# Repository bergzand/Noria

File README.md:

# Noria Split Keyboard

The Noria keyboard is a Kyria-based split keyboard. It has 6 colums and 3 rows
with a larger thumb cluster. Like the original Kyria it has support for both 2U
and dual 1U keys for the thumbs. There are three positions for a rotary encoder
of which one can be used at a time

The PCB can be flipped and used for both the left and right variant.

The PCB has space for a SPI NOR flash chip that can be used for user
configuration settings

## Design gotchas

- *When using a rotary encoder*: The pads for the chassis pins of the rotary
  encoder overlap with the pins for the push button. When using a rotary encoder
  with a push button the chassis pads must be manually detached (a simple knife
  will do) from *both* sides of the PCB.

- The microcontroller module and the SPI NOR flash must be on the same side of
  the PCB

- To use the reset pin, the User Information Configuration Register must be
  configured to pin 0.18 of the microntroller.

- The rotary encoder pins are connected to the NFC antenna pins of the
  microcontroller. As these pins are protected by default for NFC operations and
  will not function as rotary encoder pins. These protections must be disabled
  in the NFCPINS registers of the User Information Configuration Register.

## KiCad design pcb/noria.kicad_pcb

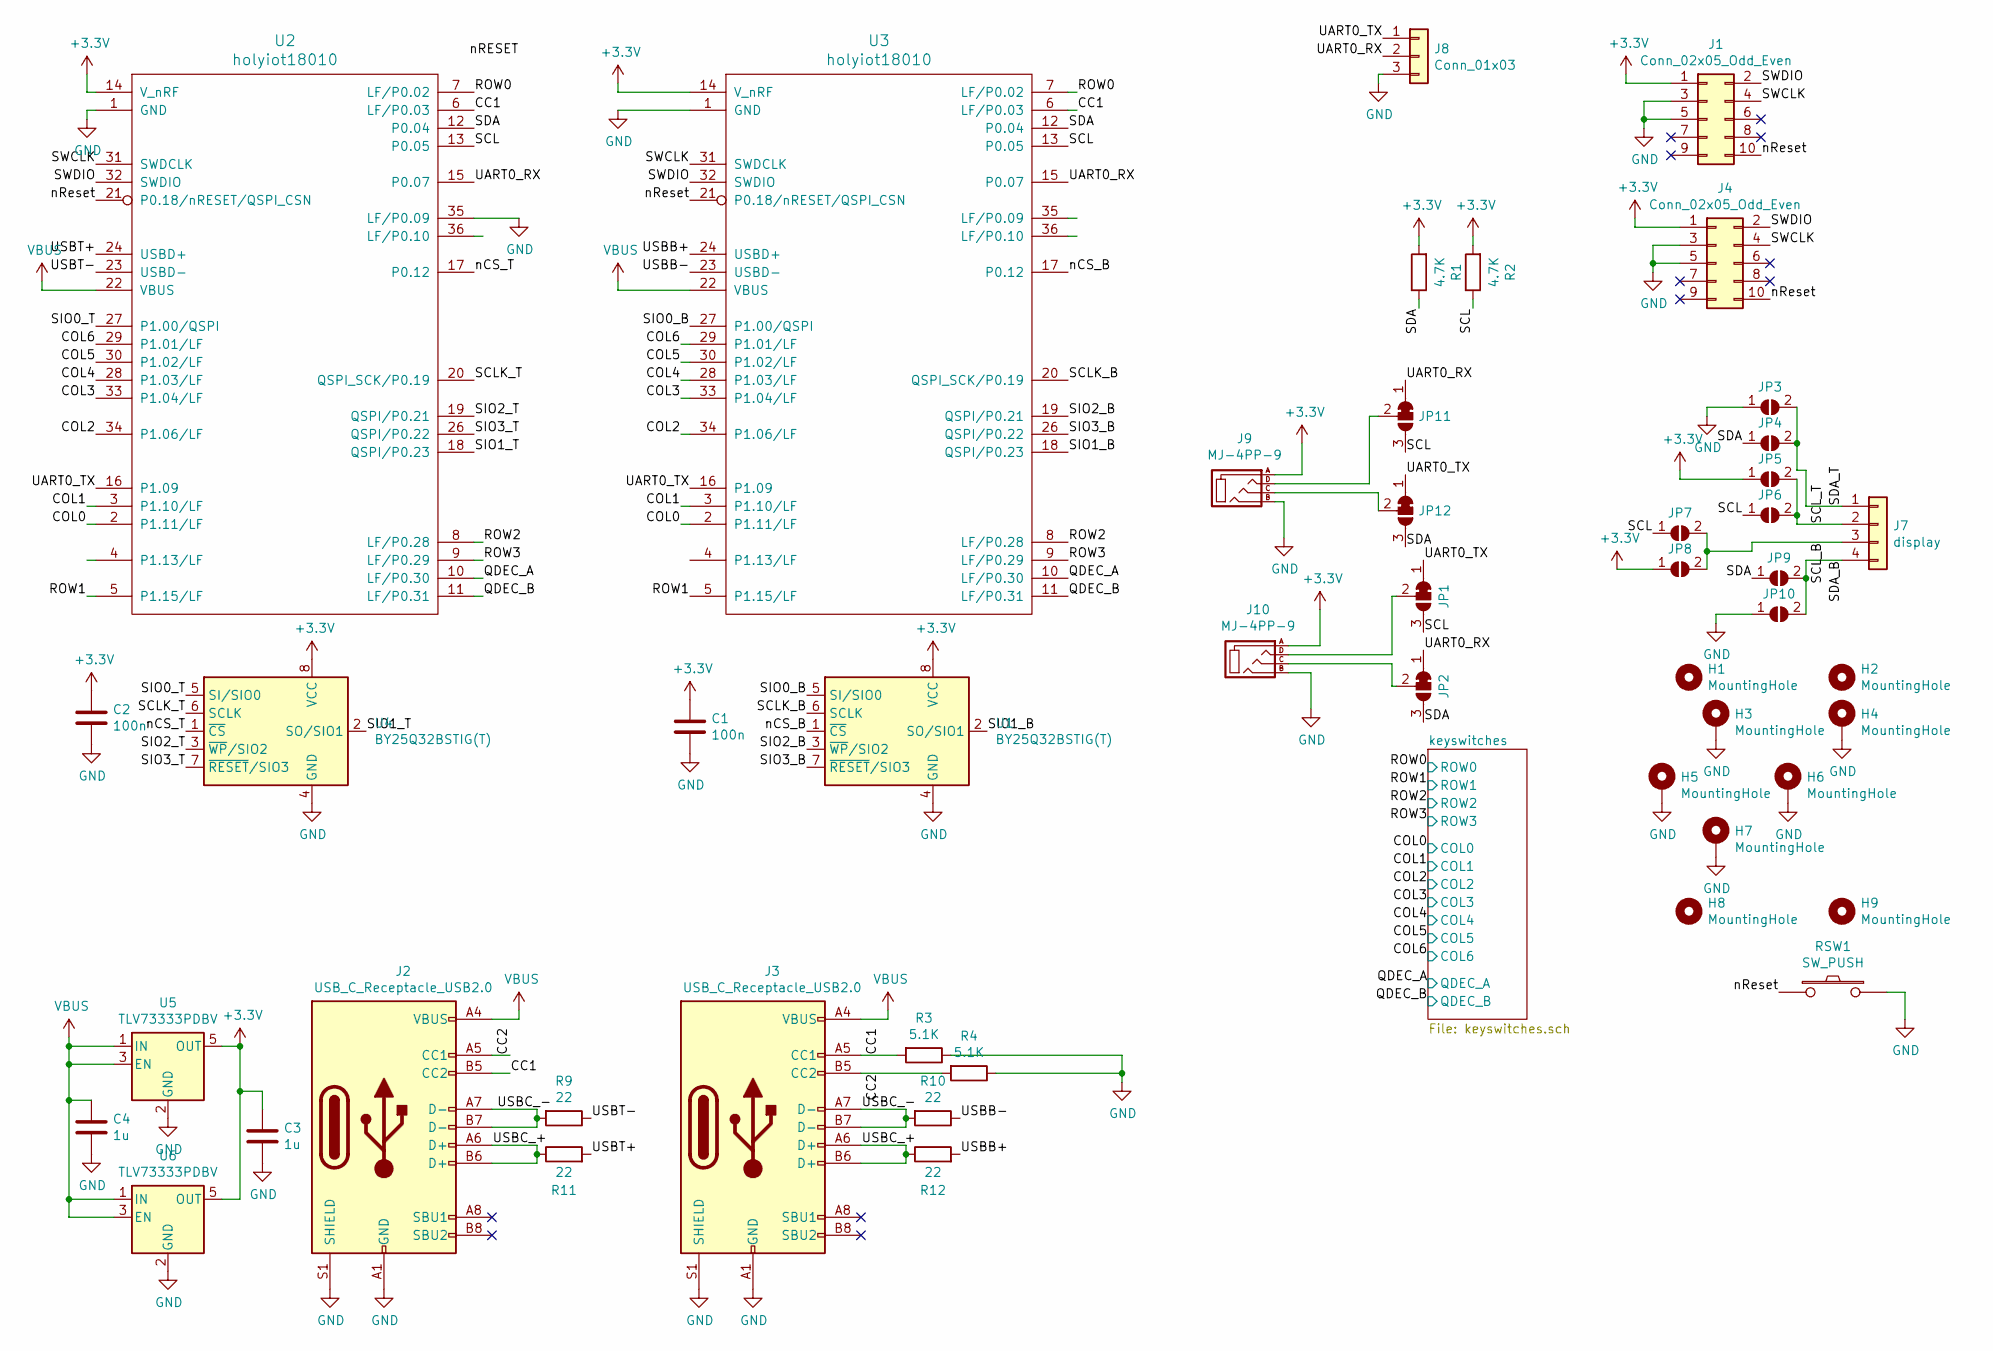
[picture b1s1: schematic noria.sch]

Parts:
C1, C2: 100n; C_0603_1608Metric_Pad1.08x0.95mm_HandSolder; LCSC C66501
C3, C4: 1u; C_0603_1608Metric_Pad1.08x0.95mm_HandSolder_mirror; LCSC C59782
H1, H2: MountingHole; spacer_m2
H3, H4, H5, H6, H7: MountingHole; MountingHole_3.5mm_Pad_Via
H8, H9: MountingHole; M2_Hole_TH
J1, J4: Conn_02x05_Odd_Even; PinHeader_2x05_P1.27mm_Vertical_SMD; LCSC C150517
J2, J3: USB_C_Receptacle_USB2.0; USB_C_Receptacle_HRO_TYPE-C-31-M-12; LCSC C165948
J7: display; PinHeader_1x04_P2.54mm_Vertical; LCSC C2718488
J8: Conn_01x03; PinHeader_1x03_P2.54mm_Vertical
J9, J10: MJ-4PP-9; MJ-4PP-9_1side; LCSC C136687
JP1, JP2, JP11, JP12: SolderJumper_3_Bridged12; SolderJumper-3_P1.3mm_Bridged12_Pad1.0x1.5mm
JP3, JP4, JP5, JP6, JP7, JP8, JP9, JP10: SolderJumper_2_Open; Jumper
R1, R2: 4.7K; R_0603_1608Metric_Pad0.98x0.95mm_HandSolder; LCSC C23162
R3, R4: 5.1K; R_0603_1608Metric_Pad0.98x0.95mm_HandSolder; LCSC C23186
R9, R10, R11, R12: 22; R_0603_1608Metric_Pad0.98x0.95mm_HandSolder; LCSC C23345
RSW1: SW_PUSH; ResetSW; LCSC C498307
U1, U4: BY25Q32BSTIG(T); SOP-8_3.9x4.9mm_P1.27mm; LCSC C394868
U2, U3: holyiot18010; holyiot18010_no_inner
U5, U6: TLV73333PDBV; SOT-23-5; LCSC C134139

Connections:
+3V3: C1.1, C2.1, C3.1, J1.1, J4.1, J9.A, J10.A, JP5.1 (A), JP8.1 (A), R1.2, R2.2, U1.8 (VCC), U2.14 (V_nRF), U3.14 (V_nRF), U4.8 (VCC), U5.5 (OUT), U6.5 (OUT)
/CC1: J2.B5 (CC2), J3.A5 (CC1), R3.2, U2.6 (LF/P0.03), U3.6 (LF/P0.03)
/CC2: J2.A5 (CC1), J3.B5 (CC2), R4.2
/COL0: U2.2 (P1.11/LF), U3.2 (P1.11/LF); also elsewhere on the board
/COL1: U2.3 (P1.10/LF), U3.3 (P1.10/LF); also elsewhere on the board
/COL2: U2.34 (P1.06/LF), U3.34 (P1.06/LF); also elsewhere on the board
/COL3: U2.33 (P1.04/LF), U3.33 (P1.04/LF); also elsewhere on the board
/COL4: U2.28 (P1.03/LF), U3.28 (P1.03/LF); also elsewhere on the board
/COL5: U2.30 (P1.02/LF), U3.30 (P1.02/LF); also elsewhere on the board
/COL6: U2.29 (P1.01/LF), U3.29 (P1.01/LF); also elsewhere on the board
/QDEC_A: U2.10 (LF/P0.30), U3.10 (LF/P0.30); also elsewhere on the board
/QDEC_B: U2.11 (LF/P0.31), U3.11 (LF/P0.31); also elsewhere on the board
/ROW0: U2.7 (LF/P0.02), U3.7 (LF/P0.02); also elsewhere on the board
/ROW1: U2.5 (P1.15/LF), U3.5 (P1.15/LF); also elsewhere on the board
/ROW2: U2.8 (LF/P0.28), U3.8 (LF/P0.28); also elsewhere on the board
/ROW3: U2.9 (LF/P0.29), U3.9 (LF/P0.29); also elsewhere on the board
/SCL: JP1.3 (B), JP6.1 (A), JP7.1 (A), JP11.3 (B), R2.1, U2.13 (P0.05), U3.13 (P0.05)
/SCLK_B: U1.6 (SCLK), U3.20 (QSPI_SCK/P0.19)
/SCLK_T: U2.20 (QSPI_SCK/P0.19), U4.6 (SCLK)
/SCL_B: J7.3, JP7.2 (B), JP8.2 (B)
/SCL_T: J7.2, JP5.2 (B), JP6.2 (B)
/SDA: JP2.3 (B), JP4.1 (A), JP9.1 (A), JP12.3 (B), R1.1, U2.12 (P0.04), U3.12 (P0.04)
/SDA_B: J7.4, JP9.2 (B), JP10.2 (B)
/SDA_T: J7.1, JP3.2 (B), JP4.2 (B)
/SIO0_B: U1.5 (SI/SIO0), U3.27 (P1.00/QSPI)
/SIO0_T: U2.27 (P1.00/QSPI), U4.5 (SI/SIO0)
/SIO1_B: U1.2 (SO/SIO1), U3.18 (QSPI/P0.23)
/SIO1_T: U2.18 (QSPI/P0.23), U4.2 (SO/SIO1)
/SIO2_B: U1.3 (~WP~/SIO2), U3.19 (QSPI/P0.21)
/SIO2_T: U2.19 (QSPI/P0.21), U4.3 (~WP~/SIO2)
/SIO3_B: U1.7 (~RESET~/SIO3), U3.26 (QSPI/P0.22)
/SIO3_T: U2.26 (QSPI/P0.22), U4.7 (~RESET~/SIO3)
/SWCLK: J1.4, J4.4, U2.31 (SWDCLK), U3.31 (SWDCLK)
/SWDIO: J1.2, J4.2, U2.32 (SWDIO), U3.32 (SWDIO)
/UART0_RX: J8.2, JP2.1 (A), JP11.1 (A), U2.15 (P0.07), U3.15 (P0.07)
/UART0_TX: J8.1, JP1.1 (A), JP12.1 (A), U2.16 (P1.09), U3.16 (P1.09)
/USBB+: R12.2, U3.24 (USBD+)
/USBB-: R10.1, U3.23 (USBD-)
/USBC_+: J2.A6 (D+), J2.B6 (D+), J3.A6 (D+), J3.B6 (D+), R11.1, R12.1
/USBC_-: J2.A7 (D-), J2.B7 (D-), J3.A7 (D-), J3.B7 (D-), R9.2, R10.2
/USBT+: R11.2, U2.24 (USBD+)
/USBT-: R9.1, U2.23 (USBD-)
/nCS_B: U1.1 (~CS), U3.17 (P0.12)
/nCS_T: U2.17 (P0.12), U4.1 (~CS)
/nReset: J1.10, J4.10, RSW1.1, U2.21 (P0.18/nRESET/QSPI_CSN), U3.21 (P0.18/nRESET/QSPI_CSN)
GND: C1.2, C2.2, C3.2, C4.2, H3.1, H4.1, H5.1, H6.1, H7.1, J1.3, J1.5, J2.A1 (GND), J2.A12 (GND), J2.B1 (GND), J2.B12 (GND), J2.S1 (SHIELD), J3.A1 (GND), J3.A12 (GND), J3.B1 (GND), J3.B12 (GND), J3.S1 (SHIELD), J4.3, J4.5, J8.3, J9.B, J10.B, JP3.1 (A), JP10.1 (A), R3.1, R4.1, RSW1.2, U1.4 (GND), U2.1 (GND), U2.35 (LF/P0.09), U3.1 (GND), U3.36 (LF/P0.10), U4.4 (GND), U5.2 (GND), U6.2 (GND); also elsewhere on the board
unnamed: J9.C, JP12.2 (C)
unnamed: J9.D, JP11.2 (C)
unnamed: J10.C, JP2.2 (C)
unnamed: J10.D, JP1.2 (C)
VBUS: C4.1, J2.A4 (VBUS), J2.A9 (VBUS), J2.B4 (VBUS), J2.B9 (VBUS), J3.A4 (VBUS), J3.A9 (VBUS), J3.B4 (VBUS), J3.B9 (VBUS), U2.22 (VBUS), U3.22 (VBUS), U5.1 (IN), U5.3 (EN), U6.1 (IN), U6.3 (EN)

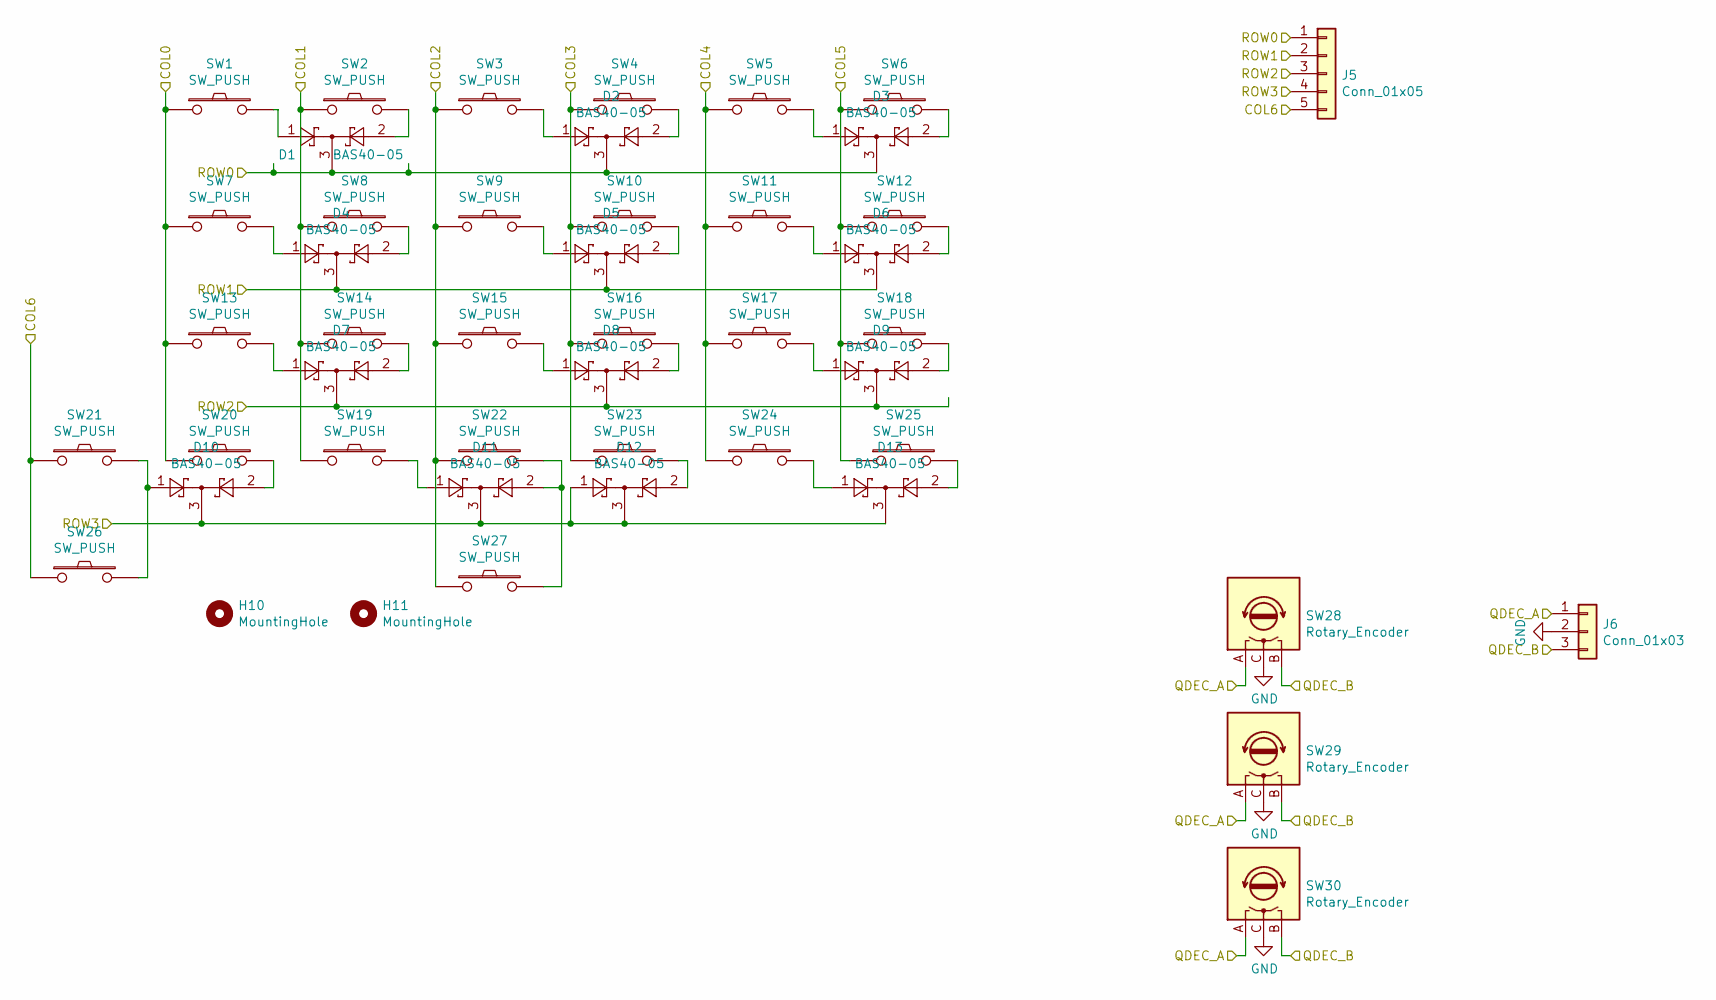
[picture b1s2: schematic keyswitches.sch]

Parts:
D1, D2, D3, D4, D5, D6, D7, D8, D9, D10, D11, D12, D13: BAS40-05; SOT-23_mirror; LCSC C699088
H10, H11: MountingHole; Stabilizer_MX_2u
J5: Conn_01x05; PinHeader_1x05_P2.54mm_Vertical
J6: Conn_01x03; PinHeader_1x03_P2.54mm_Vertical
SW1, SW2, SW3, SW4, SW5, SW6, SW7, SW8, SW9, SW10, SW11, SW12, SW13, SW14, SW15, SW16, SW17, SW18, SW19, SW20, SW21, SW22, SW23, SW24, SW25: SW_PUSH; MX_ALPS_PG1350_noLed
SW26, SW27: SW_PUSH; MX_ALPS_reduced
SW28, SW29, SW30: Rotary_Encoder; RotaryEncoder_Alps_EC11E_Vertical_H20mm

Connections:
/COL0: SW1.1, SW7.1, SW13.1, SW20.1; also elsewhere on the board
/COL1: SW2.1, SW8.1, SW14.1, SW19.1; also elsewhere on the board
/COL2: SW3.1, SW9.1, SW15.1, SW22.1, SW27.1; also elsewhere on the board
/COL3: SW4.1, SW10.1, SW16.1, SW23.1; also elsewhere on the board
/COL4: SW5.1, SW11.1, SW17.1, SW24.1; also elsewhere on the board
/COL5: SW6.1, SW12.1, SW18.1, SW25.1; also elsewhere on the board
/COL6: J5.5, SW21.1, SW26.1; also elsewhere on the board
/QDEC_A: J6.1, SW28.A, SW29.A, SW30.A; also elsewhere on the board
/QDEC_B: J6.3, SW28.B, SW29.B, SW30.B; also elsewhere on the board
/ROW0: D1.3, D2.3, D3.3, J5.1; also elsewhere on the board
/ROW1: D4.3, D5.3, D6.3, J5.2; also elsewhere on the board
/ROW2: D7.3, D8.3, D9.3, J5.3; also elsewhere on the board
/ROW3: D10.3, D11.3, D12.1, D12.3, D13.3, J5.4; also elsewhere on the board
GND: J6.2, SW28.C, SW29.C, SW30.C; also elsewhere on the board
unnamed: D1.1, SW1.2
unnamed: D1.2, SW2.2
unnamed: D2.1, SW3.2
unnamed: D2.2, SW4.2
unnamed: D3.1, SW5.2
unnamed: D3.2, SW6.2
unnamed: D4.1, SW7.2
unnamed: D4.2, SW8.2
unnamed: D5.1, SW9.2
unnamed: D5.2, SW10.2
unnamed: D6.1, SW11.2
unnamed: D6.2, SW12.2
unnamed: D7.1, SW13.2
unnamed: D7.2, SW14.2
unnamed: D8.1, SW15.2
unnamed: D8.2, SW16.2
unnamed: D9.1, SW17.2
unnamed: D9.2, SW18.2
unnamed: D10.1, SW21.2, SW26.2
unnamed: D10.2, SW20.2
unnamed: D11.1, SW19.2
unnamed: D11.2, SW22.2, SW27.2
unnamed: D12.2, SW23.2
unnamed: D13.1, SW24.2
unnamed: D13.2, SW25.2

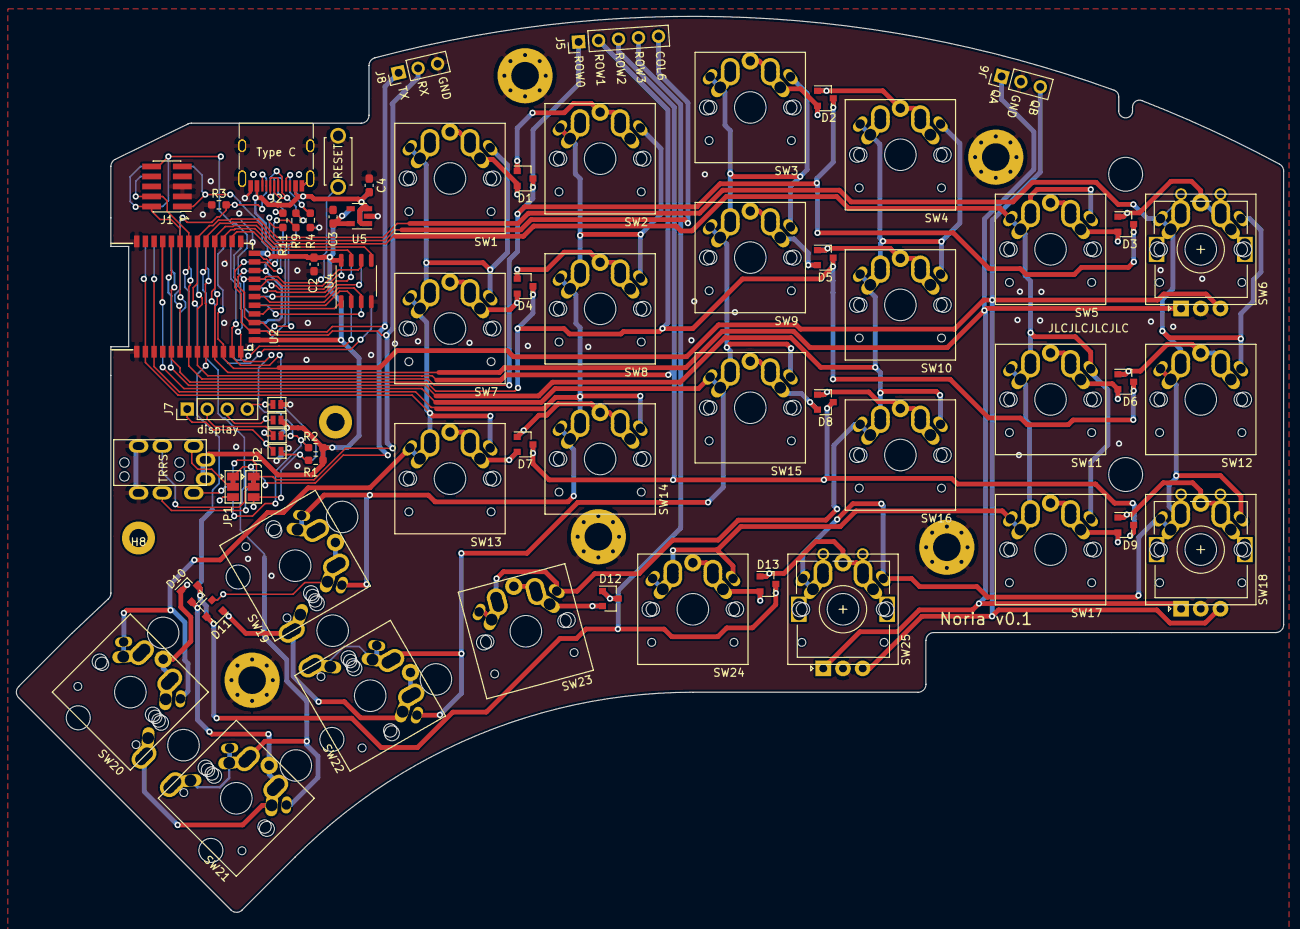
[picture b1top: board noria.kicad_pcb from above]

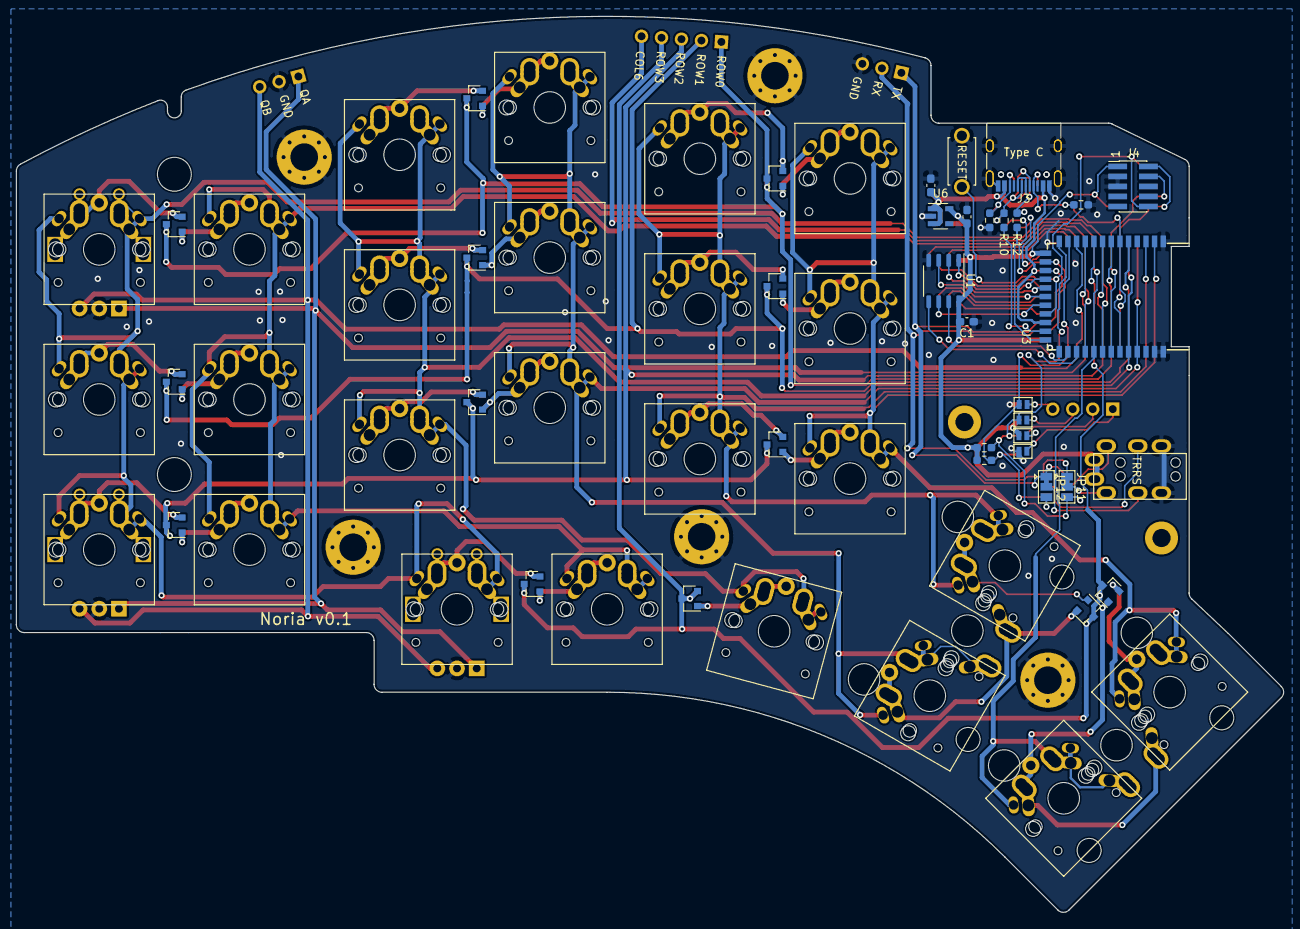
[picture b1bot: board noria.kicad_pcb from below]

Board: 2 copper layers, 160.8 x 113.7 mm, 95 parts (27 on the bottom side), 76 nets.

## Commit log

2021-10-14 Initial commit of Noria layout
2021-10-16 Add keyswitches footprints
2021-10-21 Finished iteration 1
2022-02-14 Add more Readme
2022-02-14 Add license file
2022-02-14 Add mirror version of the SOT-23 package
2022-02-14 Include gitignore
2022-02-18 Update to latest design
2022-02-18 And another update
2022-02-18 Add kicad gitignore
